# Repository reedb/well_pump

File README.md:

# well_pump
Collins Farm Well, private repository, complete

The well is 105' deep and the majority of the water comes in at 85'. 
The static water level in the well is at 15'. 

The Well Bore Water Level Sensor is just above the well pump at 80 feet.
When it reads close to zero, the pump should not be run (out of water).

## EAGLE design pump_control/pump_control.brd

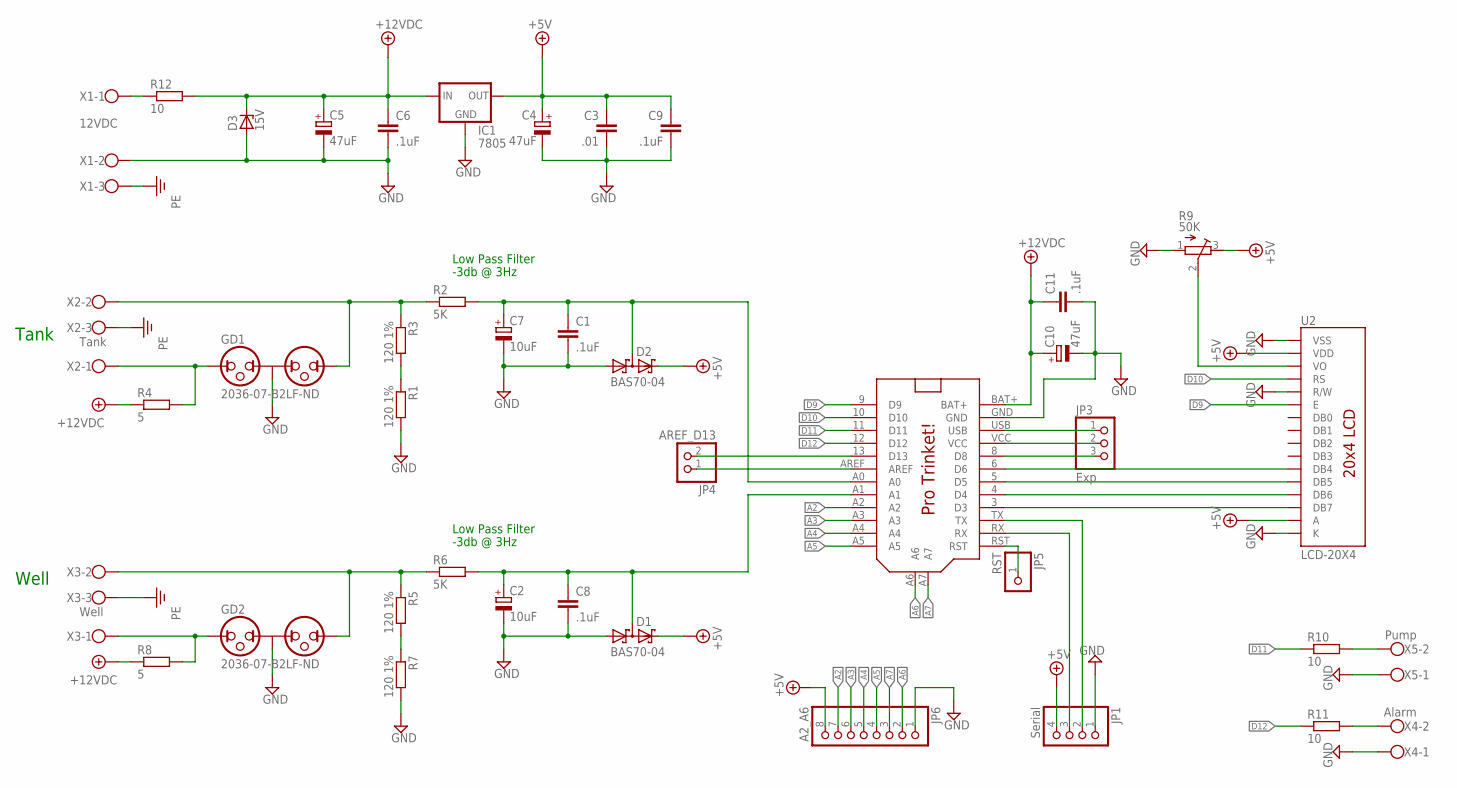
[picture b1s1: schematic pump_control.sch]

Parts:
C1, C6, C8, C9, C11: .1uF; C050-025X075
C2, C7: 10uF; E3,5-8
C3: .01; C050-025X075
C4, C5, C10: 47uF; E3,5-8
D1, D2: BAS70-04; SOT23
D3: 15V; DO35Z10
GD1, GD2: 2036-07-B2LF-ND; 2036
IC1: 7805; 78XXS
JP1: Serial; 1X04
JP3: Exp; 1X03
JP4: AREF_D13; 1X02
JP5: RST; 1X01
JP6: A2_A6; 1X08
R1, R3, R5, R7: 120 1%; 0207/10
R2, R6: 5K; 0207/10
R4, R8: 5; 0207/10
R9: 50K; RTRIM64P
R10, R11, R12: 10; 0207/10
U1: PRO_TRINKET; PROTRINKET
U2: LCD-20X4; LCD-20X4-TINSHARP
X1: 12VDC; W237-103
X2: Tank; W237-103
X3: Well; W237-103
X4: Alarm; W237-102
X5: Pump; W237-102

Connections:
12V_IN: R12.1, X1.1
+5V: C3.1, C4.+, C9.1, D1.2 (C2), D2.2 (C2), IC1.OUT, JP1.4, JP6.8, R9.3 (E), U2.2 (VDD), U2.15 (A)
+12V: C5.+, C6.1, C10.+, C11.1, D3.C, IC1.IN, R4.1, R8.1, R12.2, U1.BAT+
A0: C1.1, C7.+, D2.3 (C1A2), R2.2, U1.A0
A1: C2.+, C8.1, D1.3 (C1A2), R6.2, U1.A1
A2: JP6.7, U1.A2
A3: JP6.6, U1.A3
A4: JP6.5, U1.A4
A5: JP6.4, U1.A5
A6: JP6.2, U1.A6
A7: JP6.3, U1.A7
ALARM+: R11.2, X4.2
AREF: JP4.1, U1.AREF
D3: U1.3 (D3), U2.14 (DB7)
D4: U1.4 (D4), U2.13 (DB6)
D5: U1.5 (D5), U2.12 (DB5)
D6: U1.6 (D6), U2.11 (DB4)
D8: JP3.3, U1.8 (D8)
D9: U1.9 (D9), U2.6 (E)
D10: U1.10 (D10), U2.4 (RS)
D11: R10.1, U1.11 (D11)
D12: R11.1, U1.12 (D12)
D13: JP4.2, U1.13 (D13)
GND: C1.2, C2.-, C3.2, C4.-, C5.-, C6.2, C7.-, C8.2, C9.2, C10.-, C11.2, D1.1 (A1), D2.1 (A1), D3.A, GD1.P$2 (2), GD2.P$2 (2), IC1.GND, JP1.1, JP6.1, R1.2, R7.2, R9.1 (A), U1.GND, U2.1 (VSS), U2.5 (R/W), U2.16 (K), X1.2, X4.1, X5.1
PE: X1.3, X2.3, X3.3
PUMP+: R10.2, X5.2
R3_R1: R1.1, R3.2
R7_R5: R5.2, R7.1
RST: JP5.1, U1.RST
RX: JP1.3, U1.RX
TANK+: GD1.P$1 (1), R4.2, X2.1
TANK-: GD1.P$3 (3), R2.1, R3.1, X2.2
TX: JP1.2, U1.TX
VCC: JP3.2, U1.VCC
VO: R9.2 (S), U2.3 (VO)
VUSB: JP3.1, U1.USB
WELL+: GD2.P$1 (1), R8.2, X3.1
WELL-: GD2.P$3 (3), R5.1, R6.1, X3.2

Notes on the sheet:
-3db @ 3Hz
Low Pass Filter
Tank
Well

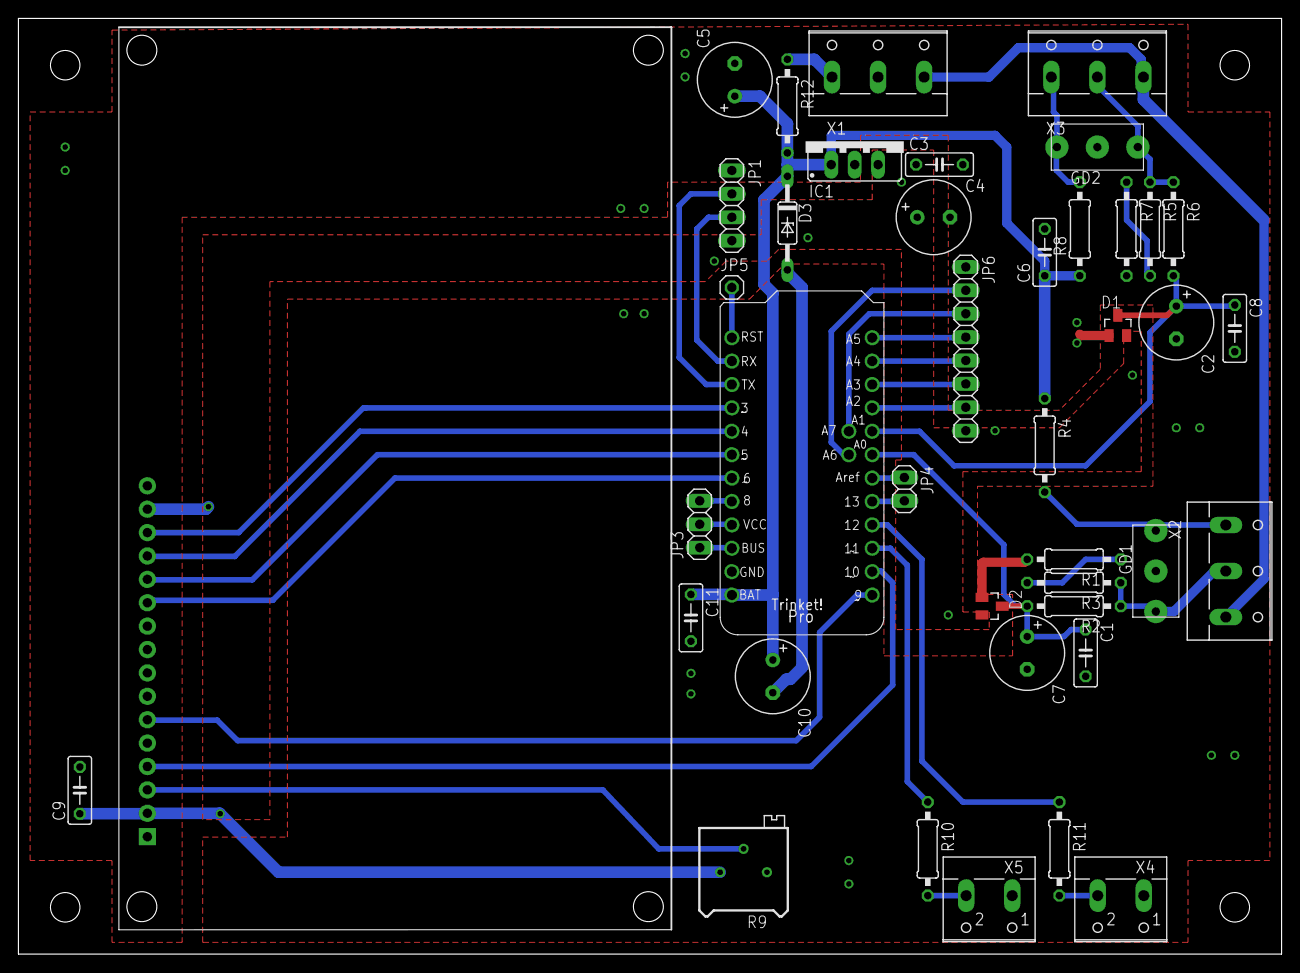
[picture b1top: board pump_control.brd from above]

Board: 2 copper layers, 137.2 x 101.6 mm, 41 parts (0 on the bottom side), 38 nets.

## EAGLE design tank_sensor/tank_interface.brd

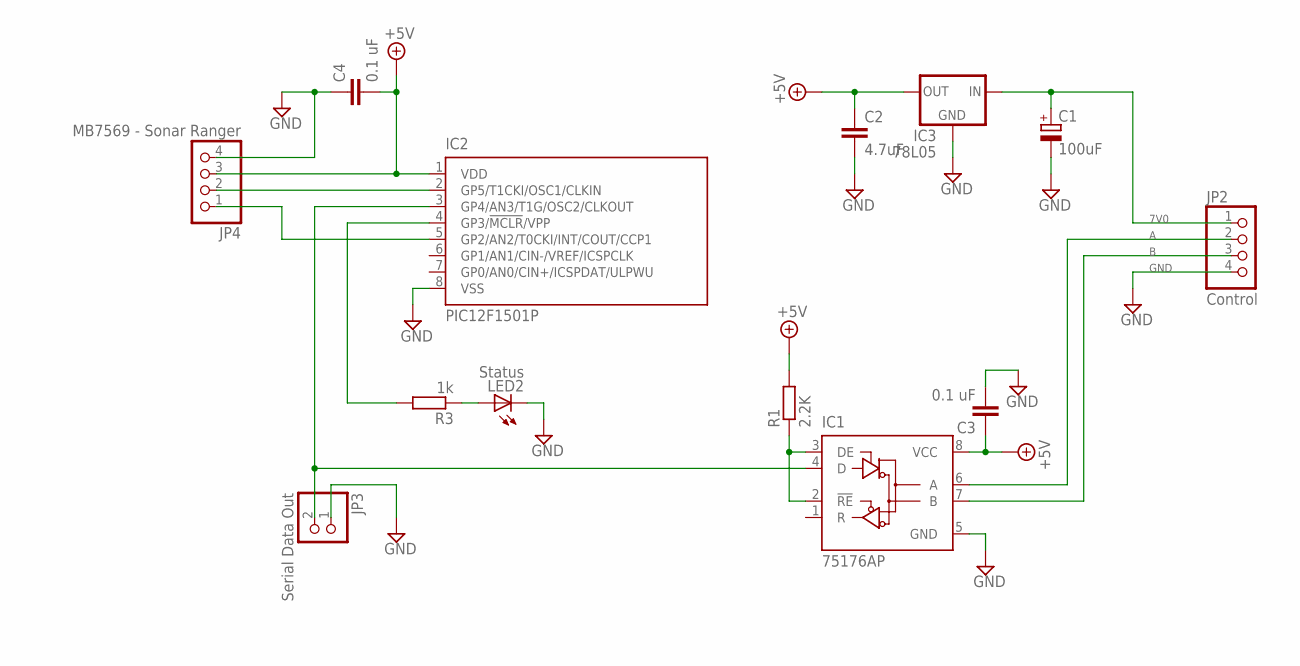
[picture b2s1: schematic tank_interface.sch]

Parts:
C1: 100uF; E2,5-7
C2: 4.7uF; C0402
C3, C4: 0.1 uF; C0402
IC1: 75176AP; DIL08
IC2: PIC12F1501P; DIL8
IC3: 78L05; 78XXS
JP2: Control; 1X04
JP3: Serial Data Out; 1X02
JP4: MB7569 - Sonar Ranger; 1X04
LED2: Status; LED3MM
R1: 2.2K; R0603
R3: 1k; R0603

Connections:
7V0: C1.+, IC3.IN, JP2.1
+5V: C2.1, C3.1, C4.2, IC1.8 (VCC), IC2.1 (VDD), IC3.OUT, JP4.3, R1.2
A: IC1.6 (A), JP2.2
B: IC1.7 (B), JP2.3
DE: IC1.2 (!RE), IC1.3 (DE), R1.1
GND: C1.-, C2.2, C3.2, C4.1, IC1.5 (GND), IC2.8 (VSS), IC3.GND, JP2.4, JP3.1, JP4.4, LED2.K (C)
unnamed: IC2.5 (GP2/AN2/T0CKI/INT/COUT/CCP1), JP4.1
unnamed: LED2.A, R3.1
SDAT_IN: IC2.2 (GP5/T1CKI/OSC1/CLKIN), JP4.2
SDAT_OUT: IC1.4 (D), IC2.3 (GP4/AN3/T1G/OSC2/CLKOUT), JP3.2
STATUS_LED: IC2.4 (GP3/!MCLR!/VPP), R3.2

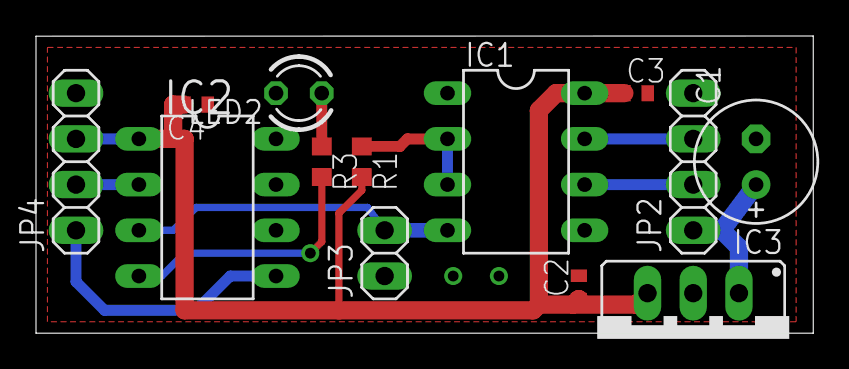
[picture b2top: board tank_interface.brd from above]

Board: 2 copper layers, 43.2 x 16.5 mm, 13 parts (0 on the bottom side), 11 nets.

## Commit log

2020-08-27 original binaries
2020-08-27 ignore intermediate files
2020-08-28 clean out spurious files
2020-08-28 Cleanup build, add 1Hz ISR
2020-08-29 build cleanup, better logging, add STATE_FILL_WAIT state
2020-08-29 add units to comments, implement fill_wait state, make State2Str return a const str (to get rid of warnings), add pump long run alarm
2020-08-30 refactor and add run time
2020-08-30 change cycling limitation to pump, remove from NextState function
2020-08-30 remove unused variable
2020-08-30 version strings
2020-08-30 fix paths
2020-08-30 tune logging
2020-08-30 fix rapid cycle fault on init
2020-08-30 build for linux
2021-05-06 firmware changes for new tanks
2021-05-06 documentation update
2021-05-06 update docs
2021-05-06 docs update for new tanks

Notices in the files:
parts and their libraries:
SparkFun-Displays: Licensing: Creative Commons ShareAlike 4.0 International - https://creativecommons.org/licenses/by-sa/4.0
